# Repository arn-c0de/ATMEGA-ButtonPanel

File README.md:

# ATmega32U4 Button Panel V1.0

> [!IMPORTANT]
> **Private Learning Project:** This is a personal experimental project focused on learning PCB design, hardware architecture, and iterative improvements.
> 
> **Feedback is welcome!** If you have suggestions for improvements or find issues, please feel free to:
> - Reach out via **private message** or email.
> - Start a topic in the **Discussions** tab.
> - Open a **Pull Request** with your proposed changes.

## Table of Contents
- [Overview](#overview)
- [Hardware Specifications](#hardware-specifications)
- [Project Status](#project-status)
- [Technical Reference](#technical-reference)
- [Security](#security)

---

## Overview
FlightPanel-01 is a custom input controller based on the **ATmega32U4** (Arduino Pro Micro compatible). This project serves as a bridge for migrating an older design into a new, consolidated prototype. It features a high-density input matrix using a 16-channel multiplexer to support a variety of flight simulation controls.

## Hardware Specifications
- **MCU:** ATmega32U4 (TQFP-44)
- **Multiplexer:** CD74HC4067M (16-Channel Analog Mux/Demux)
- **Inputs:**
  - 8x Toggle Switches (via Mux)
  - 11x Tactile Push Buttons (8 via Mux, 3 direct)
  - 1x Rotary Encoder with Push Button (direct)
  - 3x Potentiometers (Analog)
- **Outputs:**
  - 4x Cathode-driven LEDs (PWM capable)

## Project Status
This repository is currently in the **prototype and migration phase**. The schematic and initial PCB layouts are being refined to ensure compatibility between legacy code and the new hardware architecture.

## Technical Reference
For detailed pin mappings, multiplexer channel assignments, and component connections, please refer to the [PINOUT_REFERENCE.md](PINOUT_REFERENCE.md).

---

## Security
If you discover any security-related issues, please contact the maintainer directly:
📧 **arn-c0de@protonmail.com**

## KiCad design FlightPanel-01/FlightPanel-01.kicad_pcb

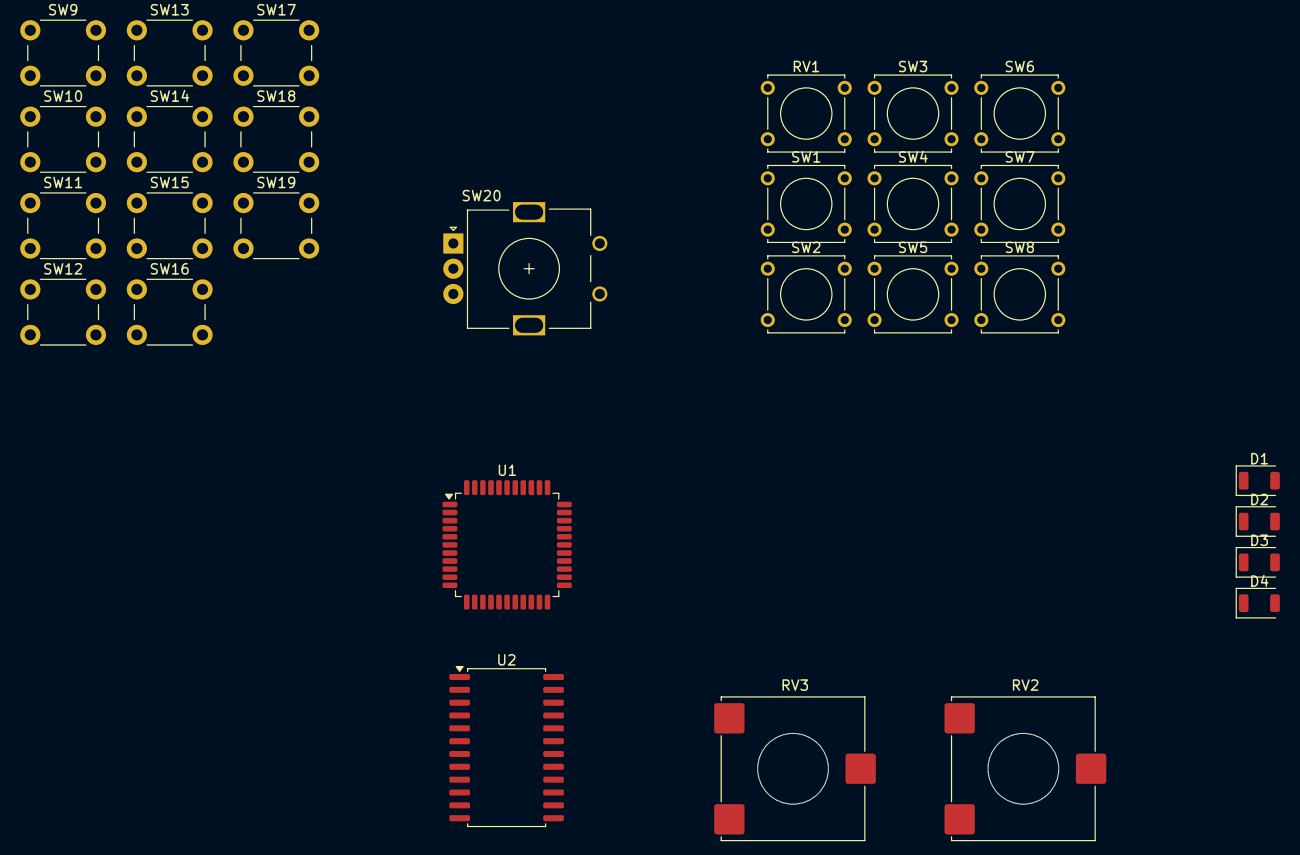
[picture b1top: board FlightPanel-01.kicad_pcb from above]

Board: 2 copper layers, 29 parts (0 on the bottom side), 9 nets, no tracks yet.

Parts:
D1, D2, D3, D4: LED; LED_1206_3216Metric_ReverseMount_Hole1.8x2.4mm
RV1: R_Potentiometer; SW_Tactile_Straight_KSA0Axx1LFTR
RV2, RV3: R_Potentiometer; Potentiometer_ACP_CA14-VSMD_Vertical_Hole
SW1, SW2, SW3, SW4, SW5, SW6, SW7, SW8: SW_SPST; SW_Tactile_Straight_KSA0Axx1LFTR
SW9, SW10, SW11, SW12, SW13, SW14, SW15, SW16, SW17, SW18, SW19: SW_Push; SW_PUSH_6mm_H8.5mm
SW20: RotaryEncoder_Switch; RotaryEncoder_Alps_EC11E_Vertical_H20mm
U1: ATmega32U4-A; TQFP-44_10x10mm_P0.8mm
U2: CD74HC4067M; SOIC-24W_7.5x15.4mm_P1.27mm

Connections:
unnamed: D1.1 (K), U1.5
unnamed: D2.1 (K), U1.6
unnamed: D3.1 (K), U1.7
unnamed: D4.1 (K), U1.8
unnamed: SW1.2 (B), SW8.2 (B)
unnamed: SW10.1, SW13.1, SW14.1
unnamed: SW16.2, U1.16
unnamed: SW17.2, U1.15
unnamed: SW18.2, U1.14

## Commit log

2026-03-12 shematic uplaod
2026-03-12 docs: update README and add technical pinout reference
2026-03-12 docs: add learning project note and feedback invitation to README
2026-03-12 sec fix
2026-03-12 init
2026-03-12 docs: add hardware image to README
2026-03-12 add img hardware v00
2026-03-12 add 3D design/files
2026-03-12 Aktualisieren von README.md
